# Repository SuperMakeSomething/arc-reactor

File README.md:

# arc-reactor

Arduino code, PCB schematic, and assembly drawing for DIY 3D printed arc reactor featured in Super Make Something Episode 15

Instructions for this project can be found here: https://youtu.be/QTlXr9m182c

by: Alex - Super Make Something

date: March, 31st, 2018

Notes:

STL files for the project can be downloaded here: https://www.thingiverse.com/thing:2846137

Like this project and want to support Super Make Something?  You can buy me a coffee here: https://www.buymeacoffee.com/SuperMakeSmthng

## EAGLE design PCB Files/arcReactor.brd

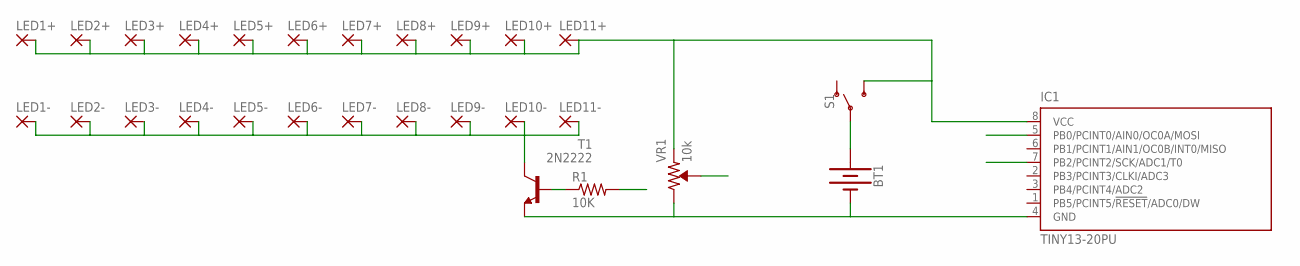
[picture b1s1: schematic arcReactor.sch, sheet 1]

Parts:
BT1: BATTERY-20MM_PTH; BATTCOM_20MM_PTH
IC1: TINY13-20PU; DIL08
LED1+, LED1-, LED2+, LED2-, LED3+, LED3-, LED4+, LED4-, LED5+, LED5-, LED6+, LED6-, LED7+, LED7-, LED8+, LED8-, LED9+, LED9-, LED10+, LED10-, LED11+, LED11-: SMD2; SMD1,27-2,54
R1: 10K; 0204V
S1: SWITCH-SPDT-PTH-11.6X4.0MM; SWITCH_SPDT_PTH_11.6X4.0MM
T1: 2N2222; TO92-EBC-OVAL
VR1: 10k; TRIMPOT-PTH-3386U

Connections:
unnamed: BT1.1 (+), S1.2
unnamed: BT1.2 (-), IC1.4 (GND), T1.E, VR1.3 (CW)
unnamed: IC1.8 (VCC), LED1+.1, LED2+.1, LED3+.1, LED4+.1, LED5+.1, LED6+.1, LED7+.1, LED8+.1, LED9+.1, LED10+.1, LED11+.1, S1.3 (S), VR1.1 (CCW)
unnamed: R1.1, T1.B
unnamed: LED1-.1, LED2-.1, LED3-.1, LED4-.1, LED5-.1, LED6-.1, LED7-.1, LED8-.1, LED9-.1, LED10-.1, LED11-.1, T1.C
POTSENSE: IC1.7 (PB2/PCINT2/SCK/ADC1/T0), VR1.2 (WIPER)
PWMCTRL: IC1.5 (PB0/PCINT0/AIN0/OC0A/MOSI), R1.2

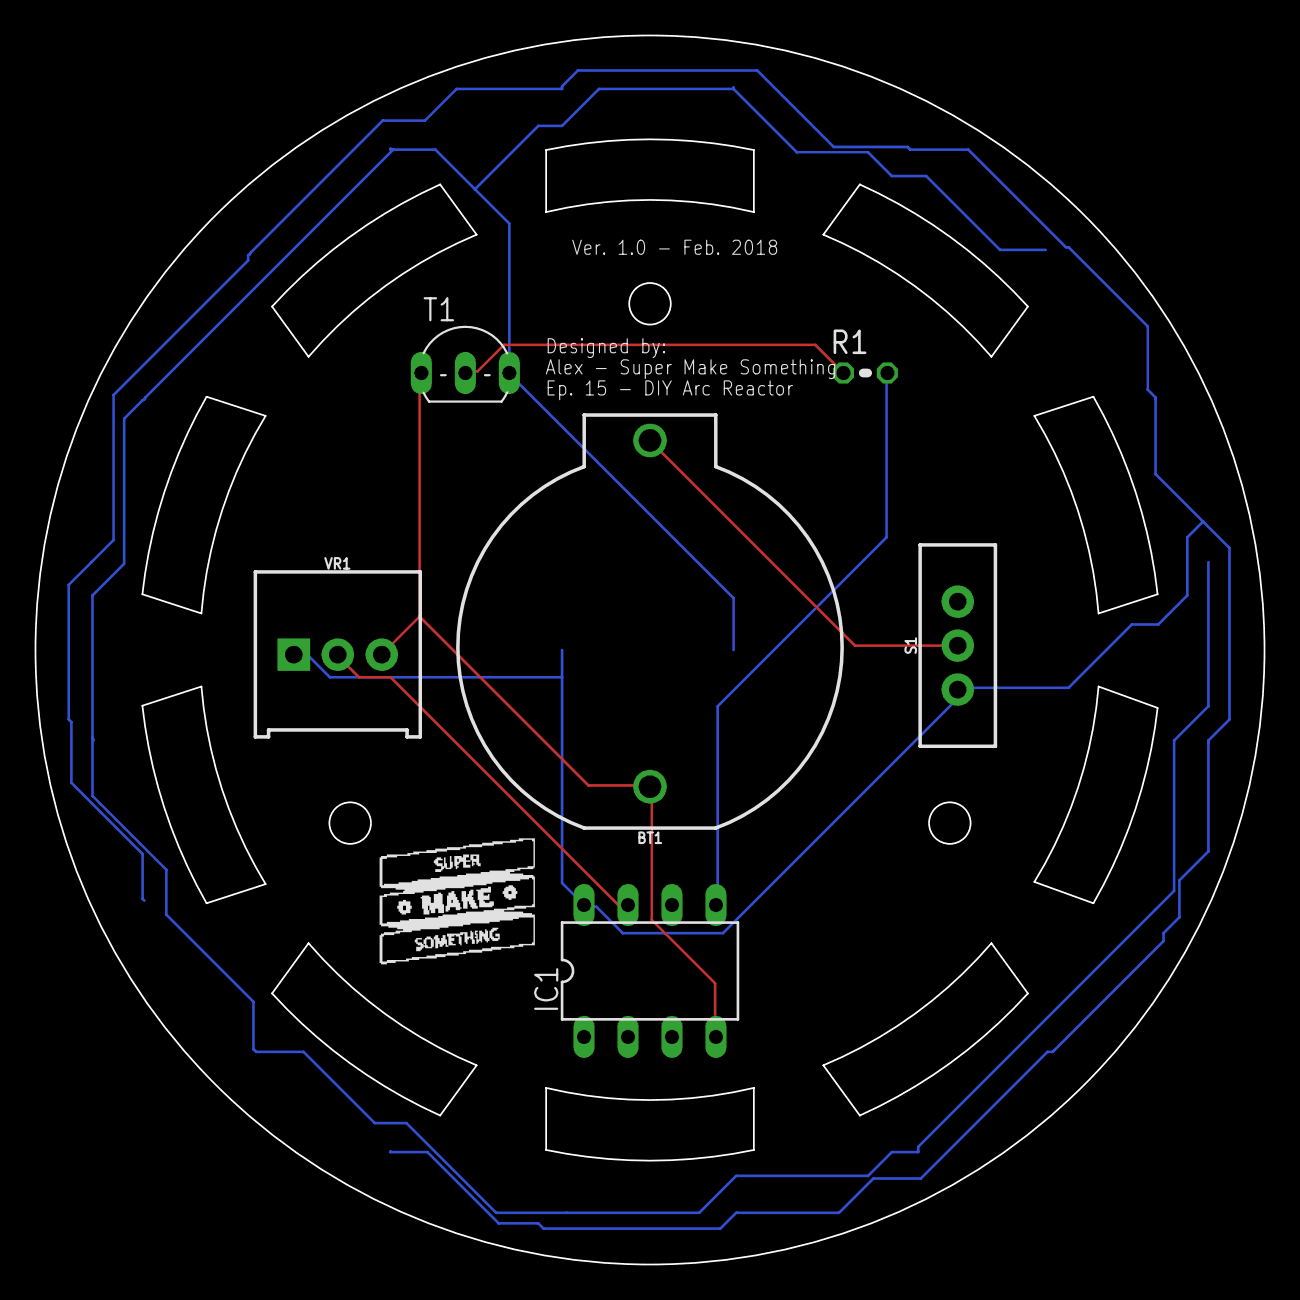
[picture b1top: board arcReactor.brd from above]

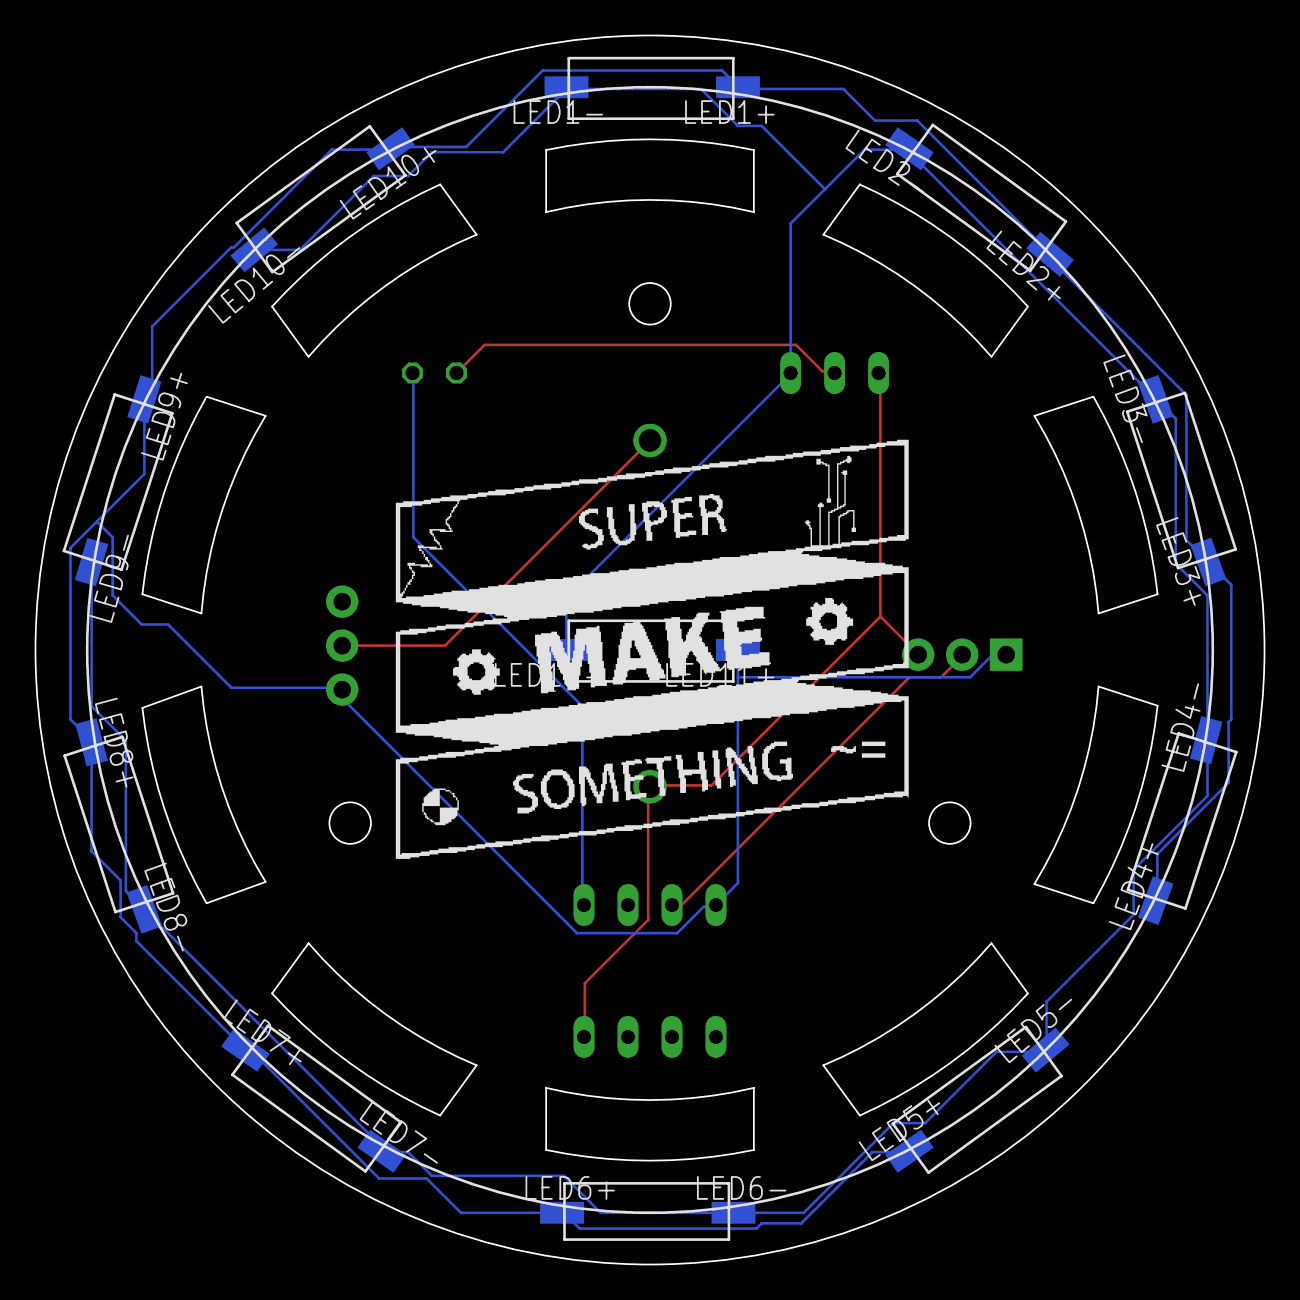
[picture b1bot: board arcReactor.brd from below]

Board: 2 copper layers, 71.0 x 71.0 mm, 28 parts (22 on the bottom side), 7 nets.

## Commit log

2018-04-01 Code, PCB design files, and assembly drawing
    Initial commit of project design files for arc reactor featured in Super Make Something Episode 15
2018-04-01 Created README.md
    Added README.
2018-04-01 Edited README.
2018-04-01 More README edits.

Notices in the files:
parts and their libraries:
SparkFun-Batteries: Licensing: Creative Commons ShareAlike 4.0 International - https://creativecommons.org/licenses/by-sa/4.0
